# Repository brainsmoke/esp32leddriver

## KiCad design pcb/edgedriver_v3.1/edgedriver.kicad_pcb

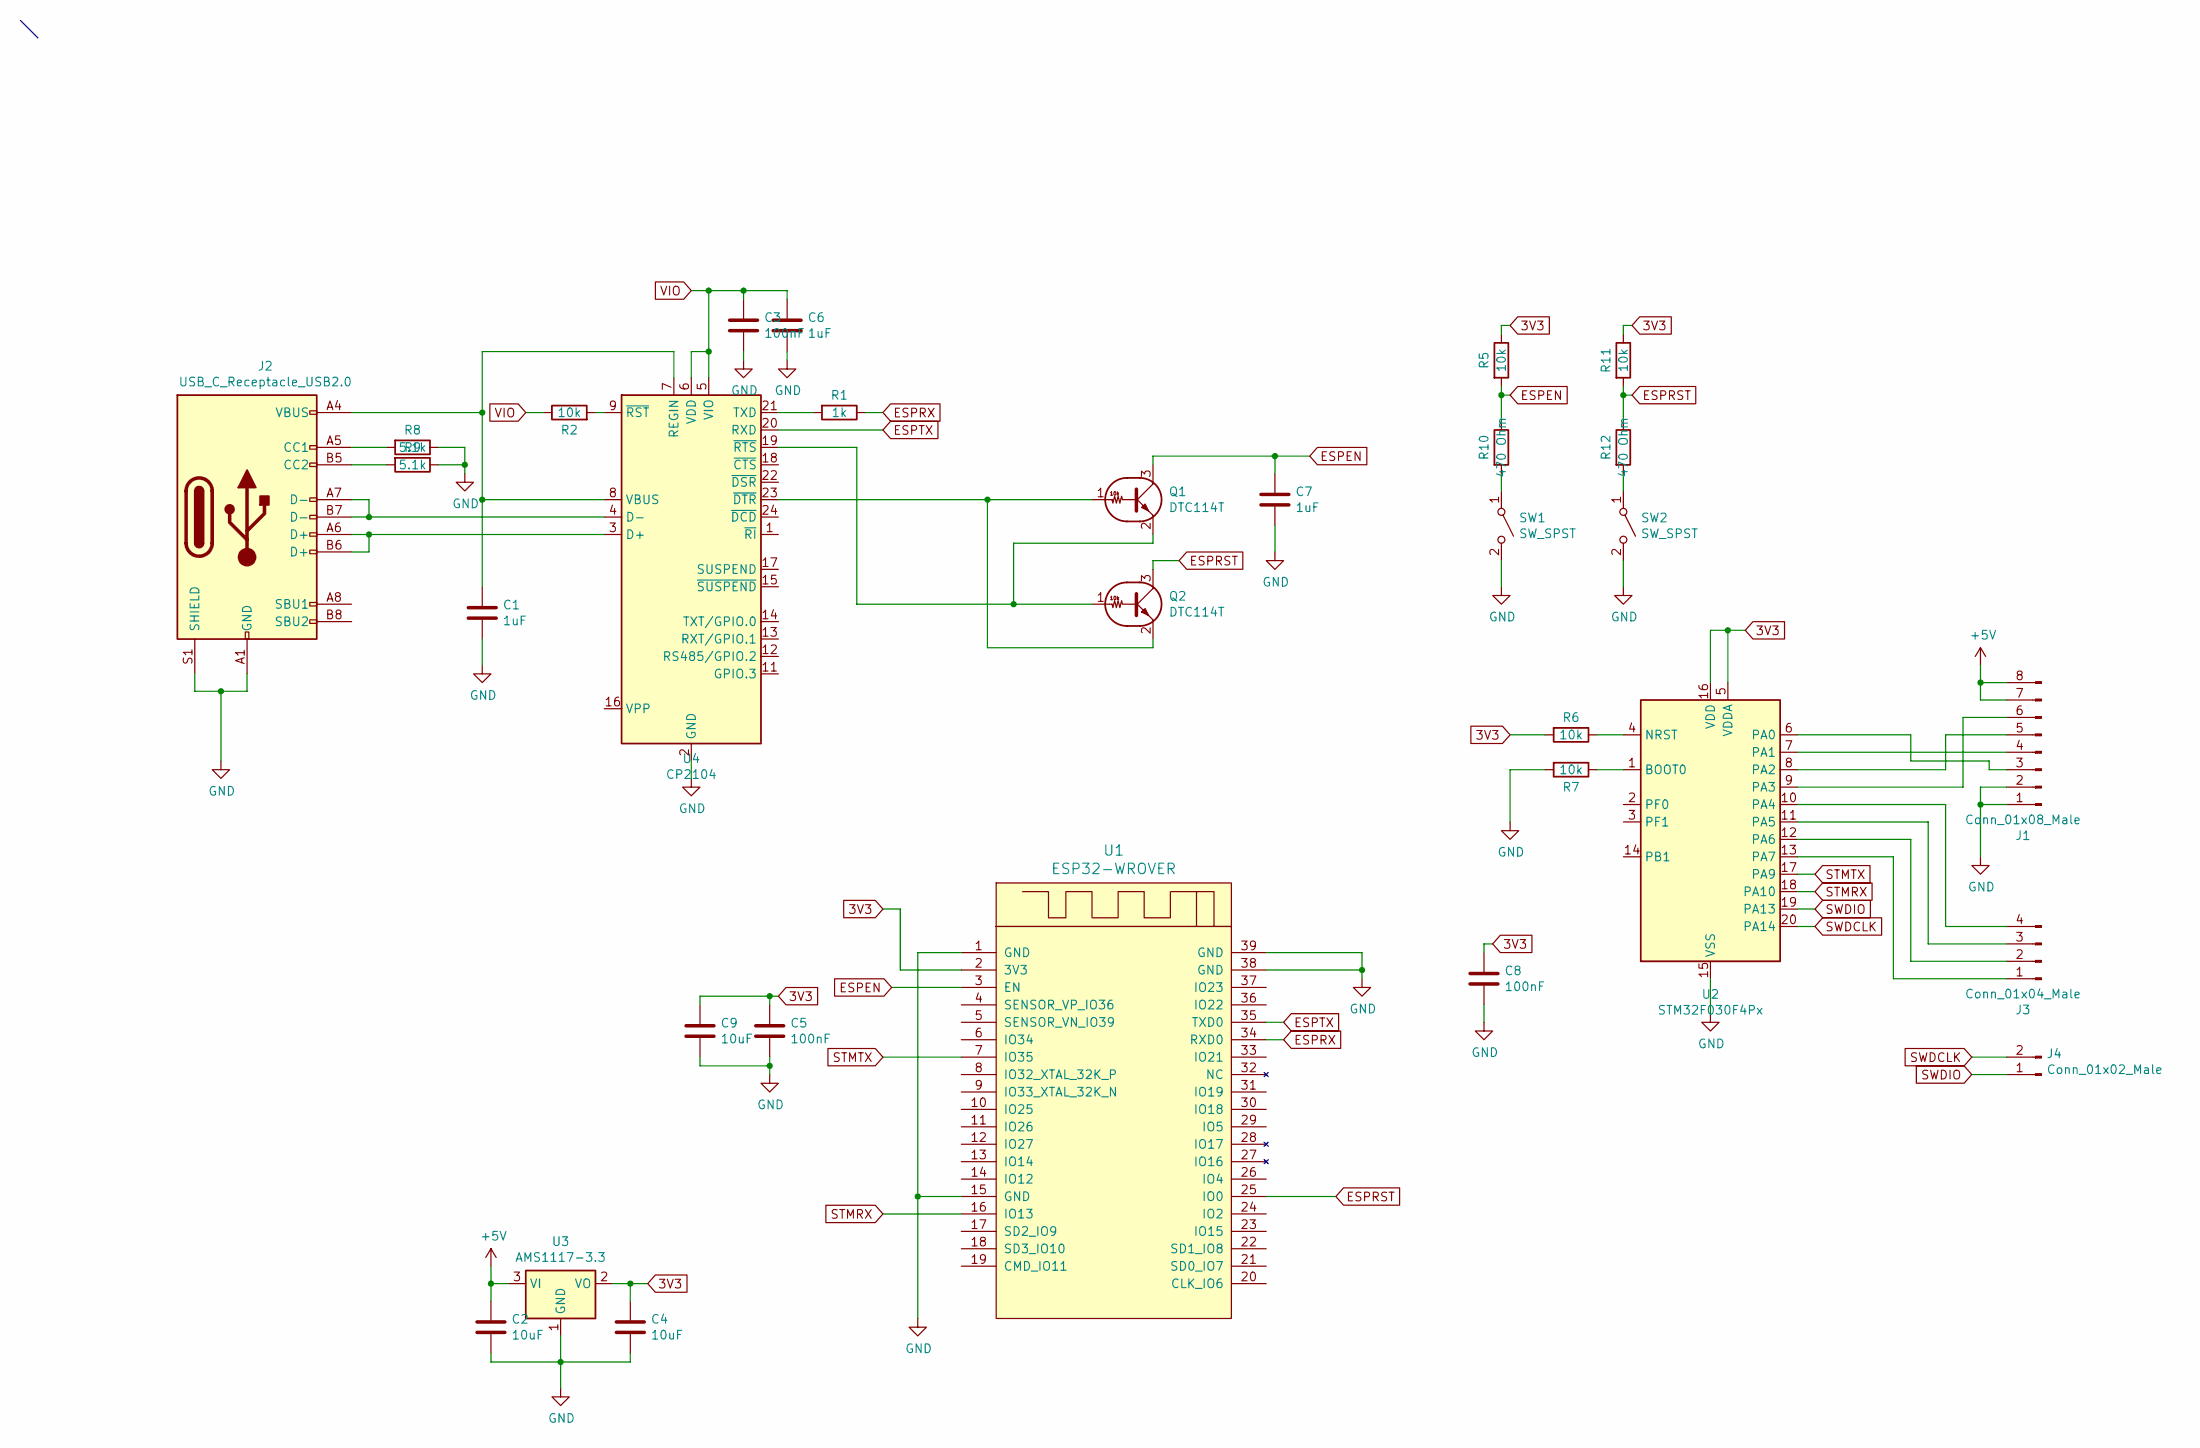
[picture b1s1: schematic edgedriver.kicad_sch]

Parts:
C1, C6, C7: 1uF; C_0402_1005Metric; LCSC C52923
C2, C4, C9: 10uF; C_0805_2012Metric; LCSC C19702
C3, C5, C8: 100nF; C_0402_1005Metric; LCSC C1525
J1: Conn_01x08_Male; PinHeader_1x08_P2.54mm_Vertical
J2: USB_C_Receptacle_USB2.0; USB_C_Receptacle_HRO_TYPE-C-31-M-12
J3: Conn_01x04_Male; PinHeader_1x04_P2.54mm_Vertical
J4: Conn_01x02_Male; PinHeader_1x02_P2.54mm_Vertical
Q1, Q2: DTC114T; SOT-523
R1: 1k; R_0402_1005Metric; LCSC C11702
R2, R5, R6, R7, R11: 10k; R_0402_1005Metric; LCSC C25744
R8, R9: 5.1k; R_0402_1005Metric; LCSC C25905
R10: 470 Ohm; R_0402_1005Metric; LCSC C25792
R12: 470 Ohm; R_0402_1005Metric; LCSC C25167
SW1, SW2: SW_SPST; SW_Push_1P1T_NO_CK_KMR2
U1: ESP32-WROVER; XCVR_ESP32-WROVER
U2: STM32F030F4Px; TSSOP-20_4.4x6.5mm_P0.65mm
U3: AMS1117-3.3; SOT-223-3_TabPin2; LCSC C6186
U4: CP2104; QFN-24-1EP_4x4mm_P0.5mm_EP2.6x2.6mm; LCSC C47742

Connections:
3V3: C4.1, C5.1, C8.1, C9.1, R5.1, R6.2, R11.1, U1.2 (3V3), U2.5 (VDDA), U2.16 (VDD), U3.2 (VO)
+5V: C2.1, J1.7, J1.8, U3.3 (VI)
ESPEN: C7.1, Q1.3 (C), R5.2, R10.1, U1.3 (EN)
ESPRST: Q2.3 (C), R11.2, R12.1, U1.25 (IO0)
ESPRX: R1.1, U1.34 (RXD0)
ESPTX: U1.35 (TXD0), U4.20 (RXD)
GND: C1.2, C2.2, C3.2, C4.2, C5.2, C6.2, C7.2, C8.2, C9.2, J1.1, J1.2, J2.A1 (GND), J2.A12 (GND), J2.B1 (GND), J2.B12 (GND), J2.S1 (SHIELD), R7.2, R8.1, R9.1, SW1.2 (B), SW2.2 (B), U1.1 (GND), U1.15 (GND), U1.38 (GND), U1.39 (GND), U2.15 (VSS), U3.1 (GND), U4.2 (GND), U4.25 (GND)
unnamed: J1.3, U2.6 (PA0)
unnamed: J1.4, U2.7 (PA1)
unnamed: J1.5, U2.8 (PA2)
unnamed: J1.6, U2.9 (PA3)
unnamed: J2.A5 (CC1), R8.2
unnamed: J2.B5 (CC2), R9.2
unnamed: J3.1, U2.13 (PA7)
unnamed: J3.2, U2.12 (PA6)
unnamed: J3.3, U2.11 (PA5)
unnamed: J3.4, U2.10 (PA4)
unnamed: Q1.1 (B), Q2.2 (E), U4.23 (~DTR)
unnamed: Q1.2 (E), Q2.1 (B), U4.19 (~RTS)
unnamed: R10.2, SW1.1 (A)
unnamed: R12.2, SW2.1 (A)
unnamed: R7.1, U2.1 (BOOT0)
unnamed: R6.1, U2.4 (NRST)
unnamed: J2.A6 (D+), J2.B6 (D+), U4.3 (D+)
unnamed: J2.A7 (D-), J2.B7 (D-), U4.4 (D-)
unnamed: C1.1, J2.A4 (VBUS), J2.A9 (VBUS), J2.B4 (VBUS), J2.B9 (VBUS), U4.7 (REGIN), U4.8 (VBUS)
unnamed: R1.2, U4.21 (TXD)
unnamed: R2.2, U4.9 (~RST)
STMRX: U1.16 (IO13), U2.18 (PA10)
STMTX: U1.7 (IO35), U2.17 (PA9)
SWDCLK: J4.2, U2.20 (PA14)
SWDIO: J4.1, U2.19 (PA13)
VIO: C3.1, C6.1, R2.1, U4.5 (VIO), U4.6 (VDD)

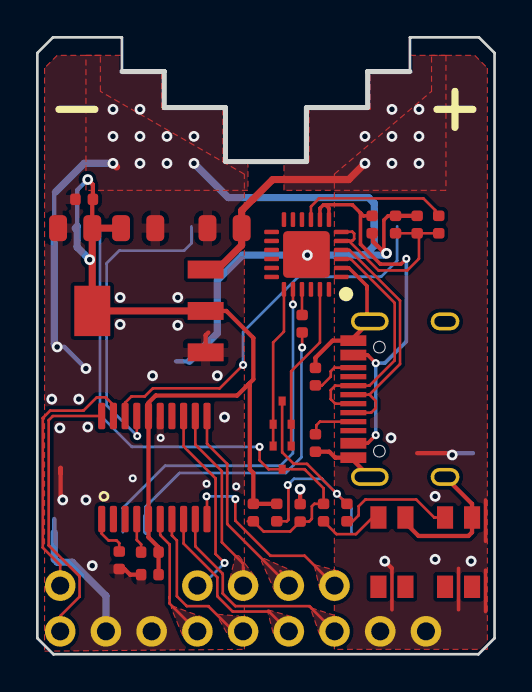
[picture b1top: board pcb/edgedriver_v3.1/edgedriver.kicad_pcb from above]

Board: 4 copper layers, 25.4 x 34.3 mm, 31 parts (1 on the bottom side), 33 nets.

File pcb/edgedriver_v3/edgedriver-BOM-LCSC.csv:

Comment,Designator,Footprint,LCSC Part Number
"10uF","C4,C2,C9","0603","C19702"
"1uF","C7,C6,C1","0603","C15849"
"100nF","C8,C5,C3","0603","C14663"
"AO3400","Q1,Q2","SOT-23-3L","C20917"
"1k","R1","0603","C21190"
"10k","R6,R7,R3,R4,R5,R2","0603","C25804"
"STM32F030F4P6","U2","TSSOP-20_4.4x6.5x0.65P","C89040"
"AMS1117-3.3","U3","SOT-223","C6186"
"CP2104","U4","QFN-24_EP_4.0x4.0x0.5P","C47742"

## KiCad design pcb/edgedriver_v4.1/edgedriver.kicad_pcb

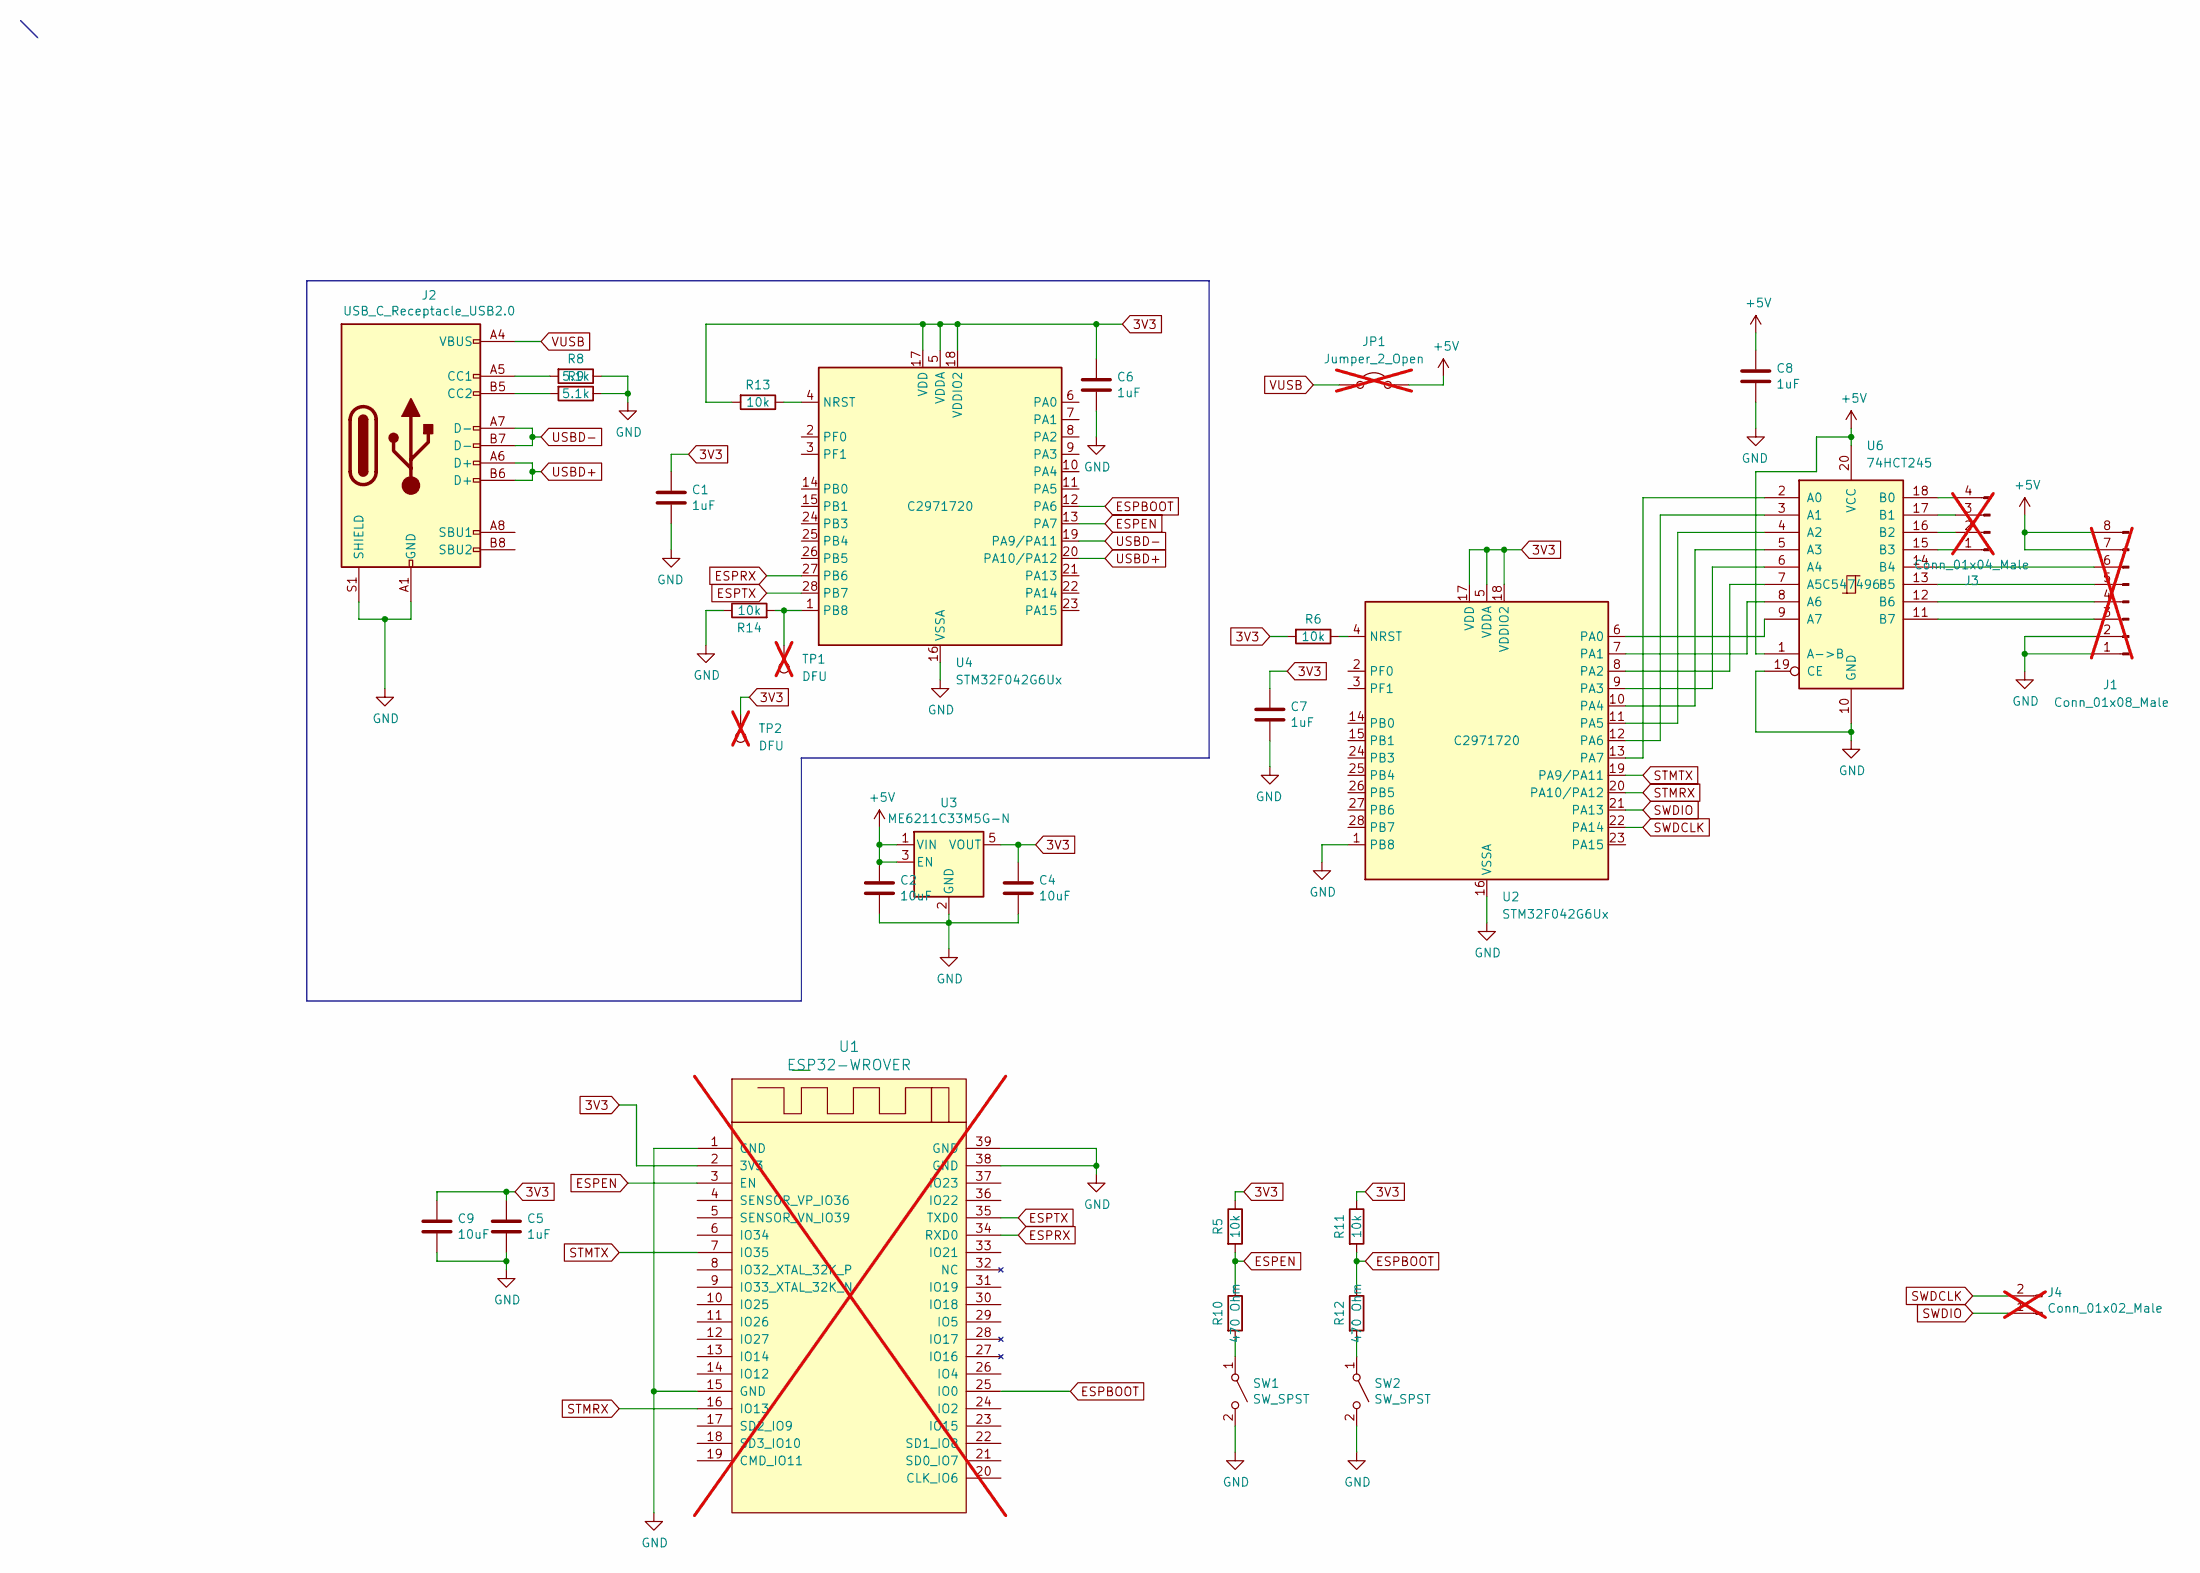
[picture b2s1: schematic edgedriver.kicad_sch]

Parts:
C1, C5, C6, C7, C8: 1uF; C_0402_1005Metric; LCSC C52923
C2, C4, C9: 10uF; C_0603_1608Metric; LCSC C19702
J1: Conn_01x08_Male; PinHeader_1x08_P2.54mm_Vertical; not fitted
J2: USB_C_Receptacle_USB2.0; USB_C_Receptacle_HRO_TYPE-C-31-M-12; LCSC C165948
J3: Conn_01x04_Male; PinHeader_1x04_P2.54mm_Vertical; not fitted
J4: Conn_01x02_Male; PinHeader_1x02_P2.54mm_Vertical; not fitted
JP1: Jumper_2_Open; R_0805_2012Metric; not fitted
R5, R6, R11, R13, R14: 10k; R_0402_1005Metric; LCSC C25744
R8, R9: 5.1k; R_0402_1005Metric; LCSC C25905
R10, R12: 470 Ohm; R_0402_1005Metric; LCSC C25117
SW1, SW2: SW_SPST; SW_Push_1P1T_NO_CK_KMR2; LCSC C318893
TP1, TP2: DFU; TestPoint_Pad_D1.0mm; not fitted
U1: ESP32-WROVER; XCVR_ESP32-WROVER; not fitted
U2, U4: STM32F042G6Ux; QFN-28_4x4mm_P0.5mm; LCSC C2971720
U3: ME6211C33M5G-N; SOT-23-5; LCSC C82942
U6: 74HCT245; DHVQFN-20-1EP_2.5x4.5mm_P0.5mm_EP1x3mm; LCSC C547496

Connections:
3V3: C1.1, C4.1, C5.1, C6.1, C7.1, C9.1, R5.1, R6.2, R11.1, R13.2, TP2.1, U1.2 (3V3), U2.5 (VDDA), U2.17 (VDD), U2.18 (VDDIO2), U3.5 (VOUT), U4.5 (VDDA), U4.17 (VDD), U4.18 (VDDIO2)
+5V: C2.1, C8.1, J1.7, J1.8, JP1.2 (B), U3.1 (VIN), U3.3 (EN), U6.1 (A->B), U6.20 (VCC)
ESPBOOT: R11.2, R12.1, U1.25 (IO0), U4.12 (PA6)
ESPEN: R5.2, R10.1, U1.3 (EN), U4.13 (PA7)
ESPRX: U1.34 (RXD0), U4.27 (PB6)
ESPTX: U1.35 (TXD0), U4.28 (PB7)
GND: C1.2, C2.2, C4.2, C5.2, C6.2, C7.2, C8.2, C9.2, J1.1, J1.2, J2.A1 (GND), J2.A12 (GND), J2.B1 (GND), J2.B12 (GND), J2.S1 (SHIELD), R8.1, R9.1, R14.1, SW1.2 (B), SW2.2 (B), U1.1 (GND), U1.15 (GND), U1.38 (GND), U1.39 (GND), U2.1 (PB8), U2.16 (VSSA), U3.2 (GND), U4.16 (VSSA), U6.10 (GND), U6.19 (CE)
unnamed: J1.3, U6.11 (B7)
unnamed: J1.4, U6.12 (B6)
unnamed: J1.5, U6.13 (B5)
unnamed: J1.6, U6.14 (B4)
unnamed: J2.A5 (CC1), R8.2
unnamed: J2.B5 (CC2), R9.2
unnamed: J3.1, U6.15 (B3)
unnamed: J3.2, U6.16 (B2)
unnamed: J3.3, U6.17 (B1)
unnamed: J3.4, U6.18 (B0)
unnamed: R10.2, SW1.1 (A)
unnamed: R12.2, SW2.1 (A)
unnamed: R6.1, U2.4 (NRST)
unnamed: U2.6 (PA0), U6.9 (A7)
unnamed: U2.7 (PA1), U6.8 (A6)
unnamed: U2.8 (PA2), U6.7 (A5)
unnamed: U2.9 (PA3), U6.6 (A4)
unnamed: U2.10 (PA4), U6.5 (A3)
unnamed: U2.11 (PA5), U6.4 (A2)
unnamed: U2.12 (PA6), U6.3 (A1)
unnamed: U2.13 (PA7), U6.2 (A0)
unnamed: R13.1, U4.4 (NRST)
unnamed: R14.2, TP1.1, U4.1 (PB8)
STMRX: U1.16 (IO13), U2.20 (PA10/PA12)
STMTX: U1.7 (IO35), U2.19 (PA9/PA11)
SWDCLK: J4.2, U2.22 (PA14)
SWDIO: J4.1, U2.21 (PA13)
USBD+: J2.A6 (D+), J2.B6 (D+), U4.20 (PA10/PA12)
USBD-: J2.A7 (D-), J2.B7 (D-), U4.19 (PA9/PA11)
VUSB: J2.A4 (VBUS), J2.A9 (VBUS), J2.B4 (VBUS), J2.B9 (VBUS), JP1.1 (A)

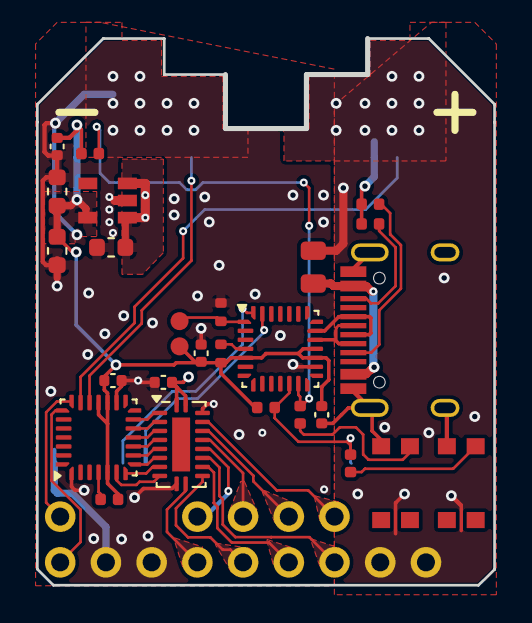
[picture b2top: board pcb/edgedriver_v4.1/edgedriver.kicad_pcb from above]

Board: 4 copper layers, 25.4 x 30.4 mm, 31 parts (1 on the bottom side), 37 nets.

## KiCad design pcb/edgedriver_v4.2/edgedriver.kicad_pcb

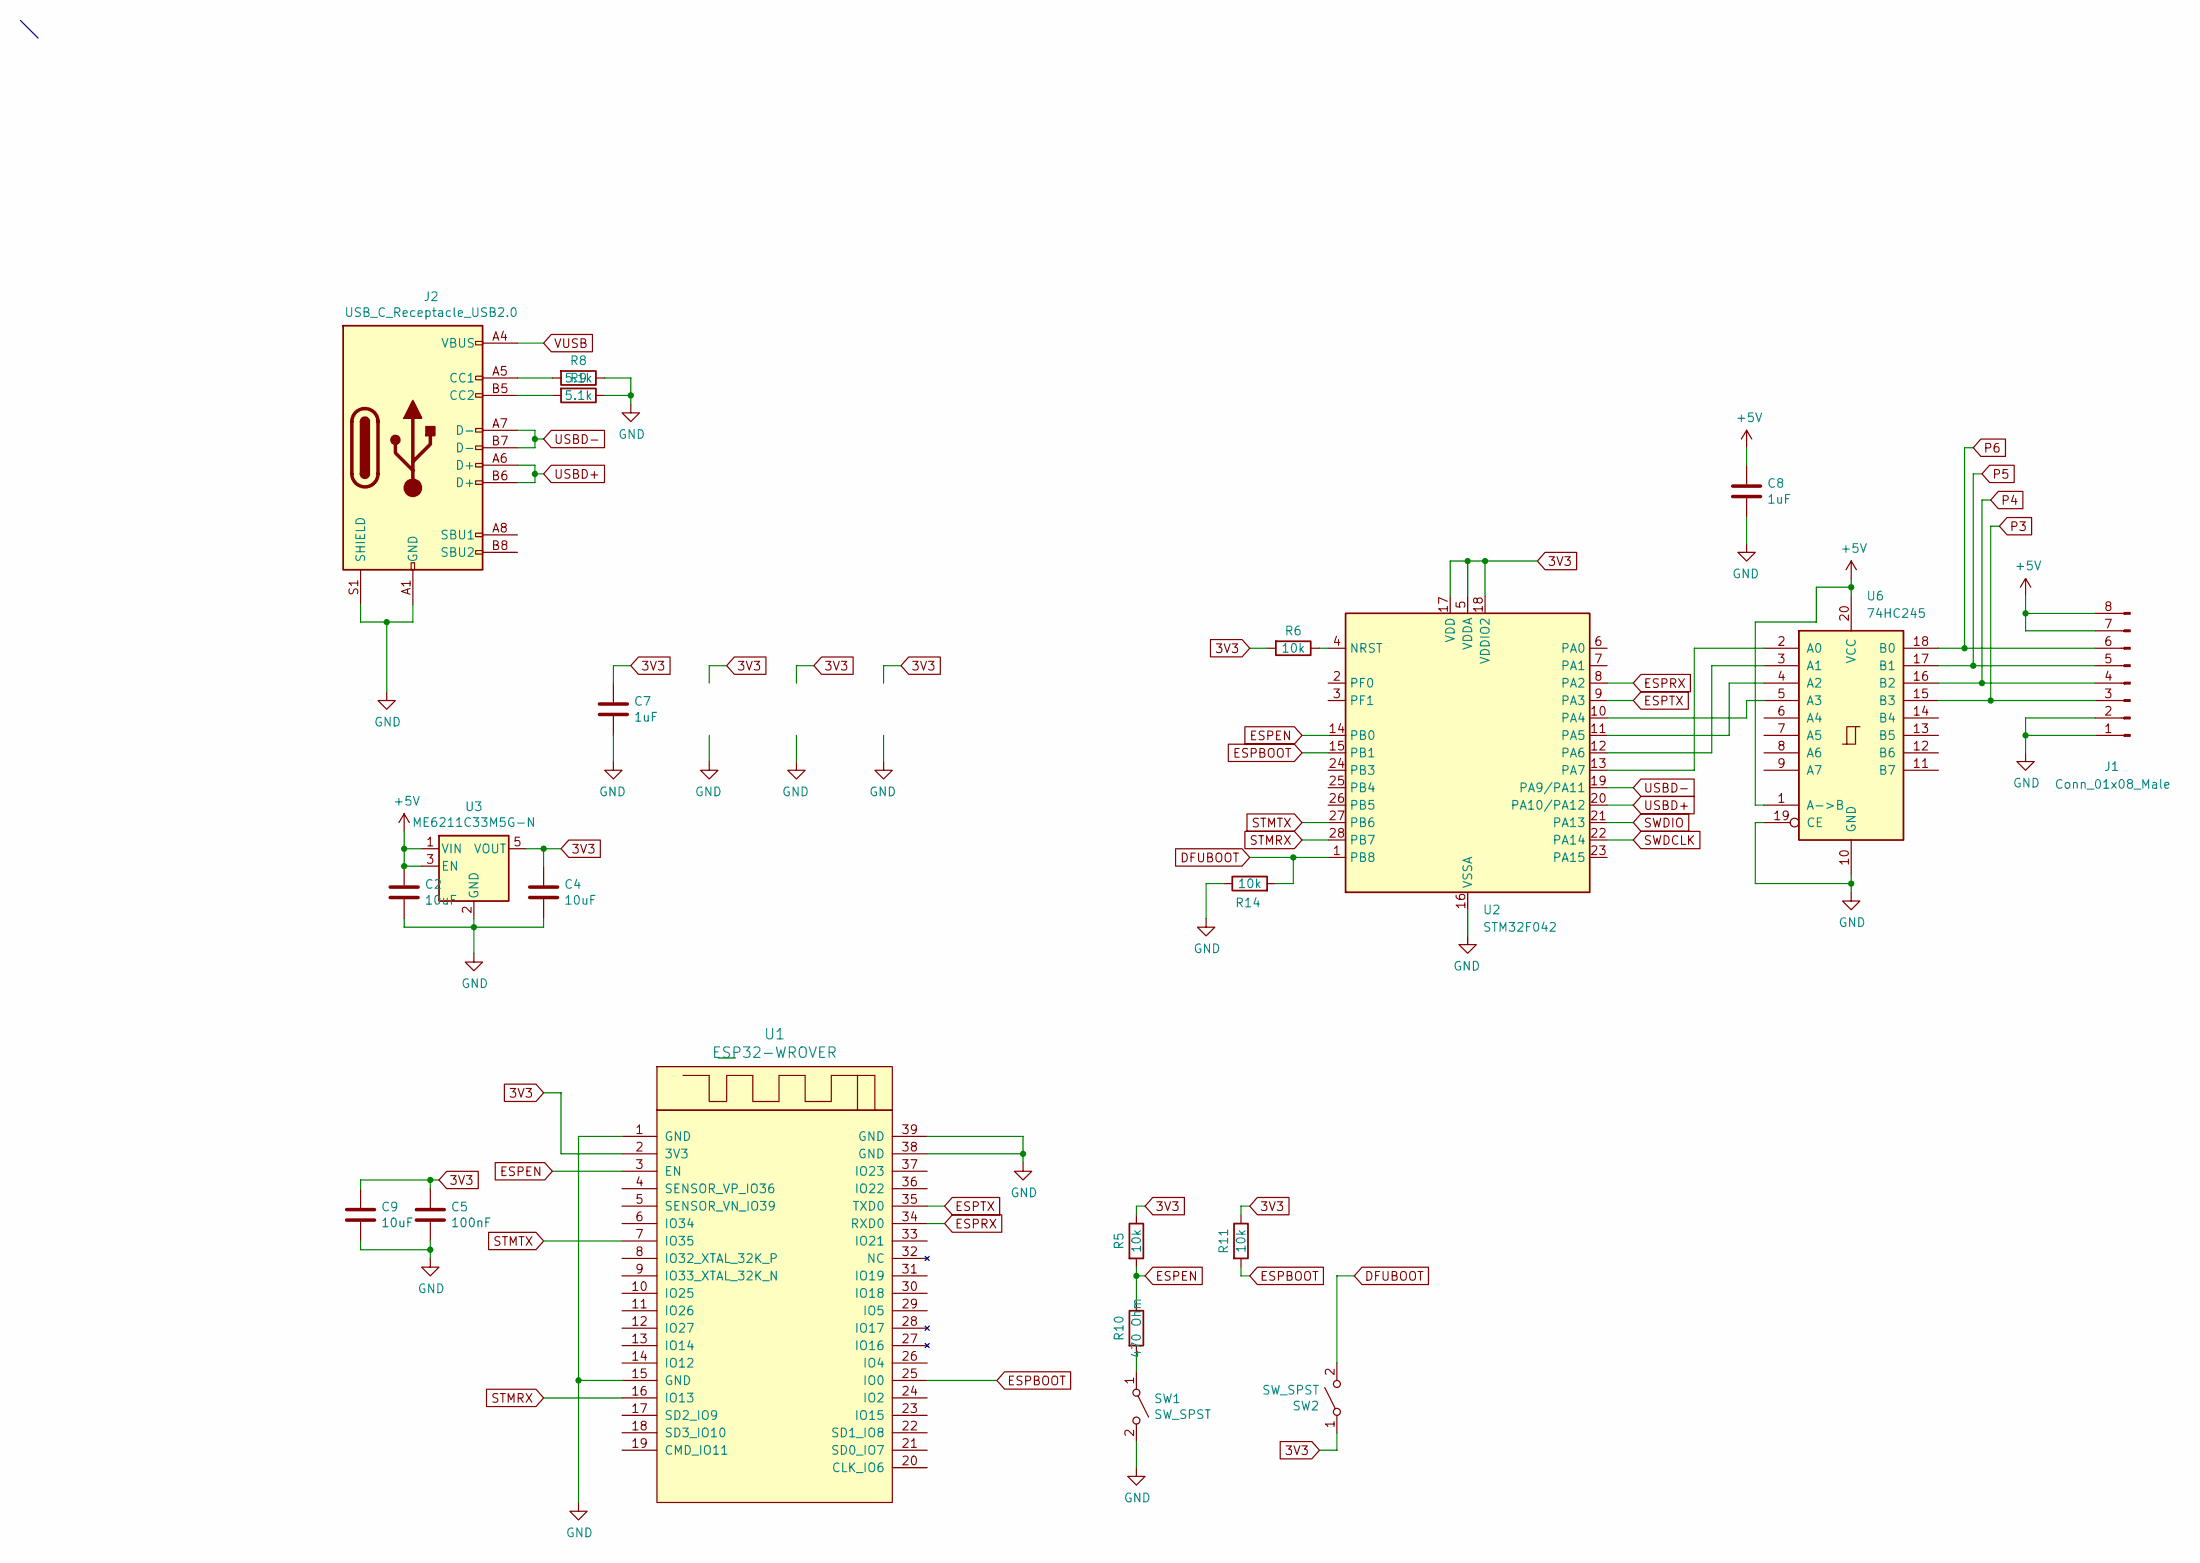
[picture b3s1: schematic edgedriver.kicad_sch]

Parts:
C2, C4, C9: 10uF; C_0603_1608Metric; LCSC C19702
C5: 100nF; C_0402_1005Metric; LCSC C1525
C7, C8: 1uF; C_0402_1005Metric; LCSC C52923
J1: Conn_01x08_Male; PinHeader_1x08_P2.54mm_Vertical
J2: USB_C_Receptacle_USB2.0; USB_C_Receptacle_HRO_TYPE-C-31-M-12; LCSC C165948
R5, R6, R11, R14: 10k; R_0402_1005Metric; LCSC C25744
R8, R9: 5.1k; R_0402_1005Metric; LCSC C25905
R10: 470 Ohm; R_0402_1005Metric; LCSC C25117
SW1, SW2: SW_SPST; SW_Push_1P1T_NO_CK_KMR2; LCSC C318893
U1: ESP32-WROVER; XCVR_ESP32-WROVER
U2: STM32F042; QFN-28_4x4mm_P0.5mm
U3: ME6211C33M5G-N; SOT-23-5; LCSC C82942
U6: 74HC245; DHVQFN-20-1EP_2.5x4.5mm_P0.5mm_EP1x3mm

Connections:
3V3: C4.1, C5.1, C7.1, C9.1, R5.1, R6.2, R11.1, SW2.1 (A), U1.2 (3V3), U2.5 (VDDA), U2.17 (VDD), U2.18 (VDDIO2), U3.5 (VOUT)
+5V: C2.1, C8.1, J1.7, J1.8, U3.1 (VIN), U3.3 (EN), U6.1 (A->B), U6.20 (VCC)
DFUBOOT: R14.2, SW2.2 (B), U2.1 (PB8)
ESPBOOT: R11.2, U1.25 (IO0), U2.15 (PB1)
ESPEN: R5.2, R10.1, U1.3 (EN), U2.14 (PB0)
ESPRX: U1.34 (RXD0), U2.8 (PA2)
ESPTX: U1.35 (TXD0), U2.9 (PA3)
GND: C2.2, C4.2, C5.2, C7.2, C8.2, C9.2, J1.1, J1.2, J2.A1 (GND), J2.A12 (GND), J2.B1 (GND), J2.B12 (GND), J2.S1 (SHIELD), R8.1, R9.1, R14.1, SW1.2 (B), U1.1 (GND), U1.15 (GND), U1.38 (GND), U1.39 (GND), U2.16 (VSSA), U3.2 (GND), U6.10 (GND), U6.19 (CE)
unnamed: J2.A5 (CC1), R8.2
unnamed: J2.B5 (CC2), R9.2
unnamed: R10.2, SW1.1 (A)
unnamed: R6.1, U2.4 (NRST)
unnamed: U2.10 (PA4), U6.5 (A3)
unnamed: U2.11 (PA5), U6.4 (A2)
unnamed: U2.12 (PA6), U6.3 (A1)
unnamed: U2.13 (PA7), U6.2 (A0)
P3: J1.3, U6.15 (B3)
P4: J1.4, U6.16 (B2)
P5: J1.5, U6.17 (B1)
P6: J1.6, U6.18 (B0)
STMRX: U1.16 (IO13), U2.28 (PB7)
STMTX: U1.7 (IO35), U2.27 (PB6)
SWDCLK: U2.22 (PA14)
SWDIO: U2.21 (PA13)
USBD+: J2.A6 (D+), J2.B6 (D+), U2.20 (PA10/PA12)
USBD-: J2.A7 (D-), J2.B7 (D-), U2.19 (PA9/PA11)
VUSB: J2.A4 (VBUS), J2.A9 (VBUS), J2.B4 (VBUS), J2.B9 (VBUS)

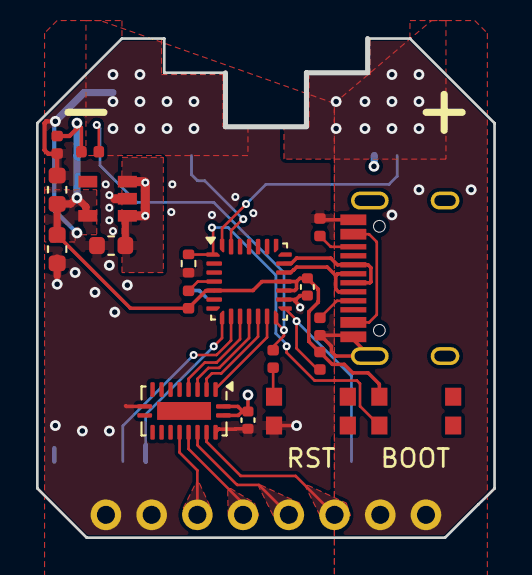
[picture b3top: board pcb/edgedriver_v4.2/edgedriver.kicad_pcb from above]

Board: 4 copper layers, 25.4 x 27.7 mm, 21 parts (1 on the bottom side), 25 nets.

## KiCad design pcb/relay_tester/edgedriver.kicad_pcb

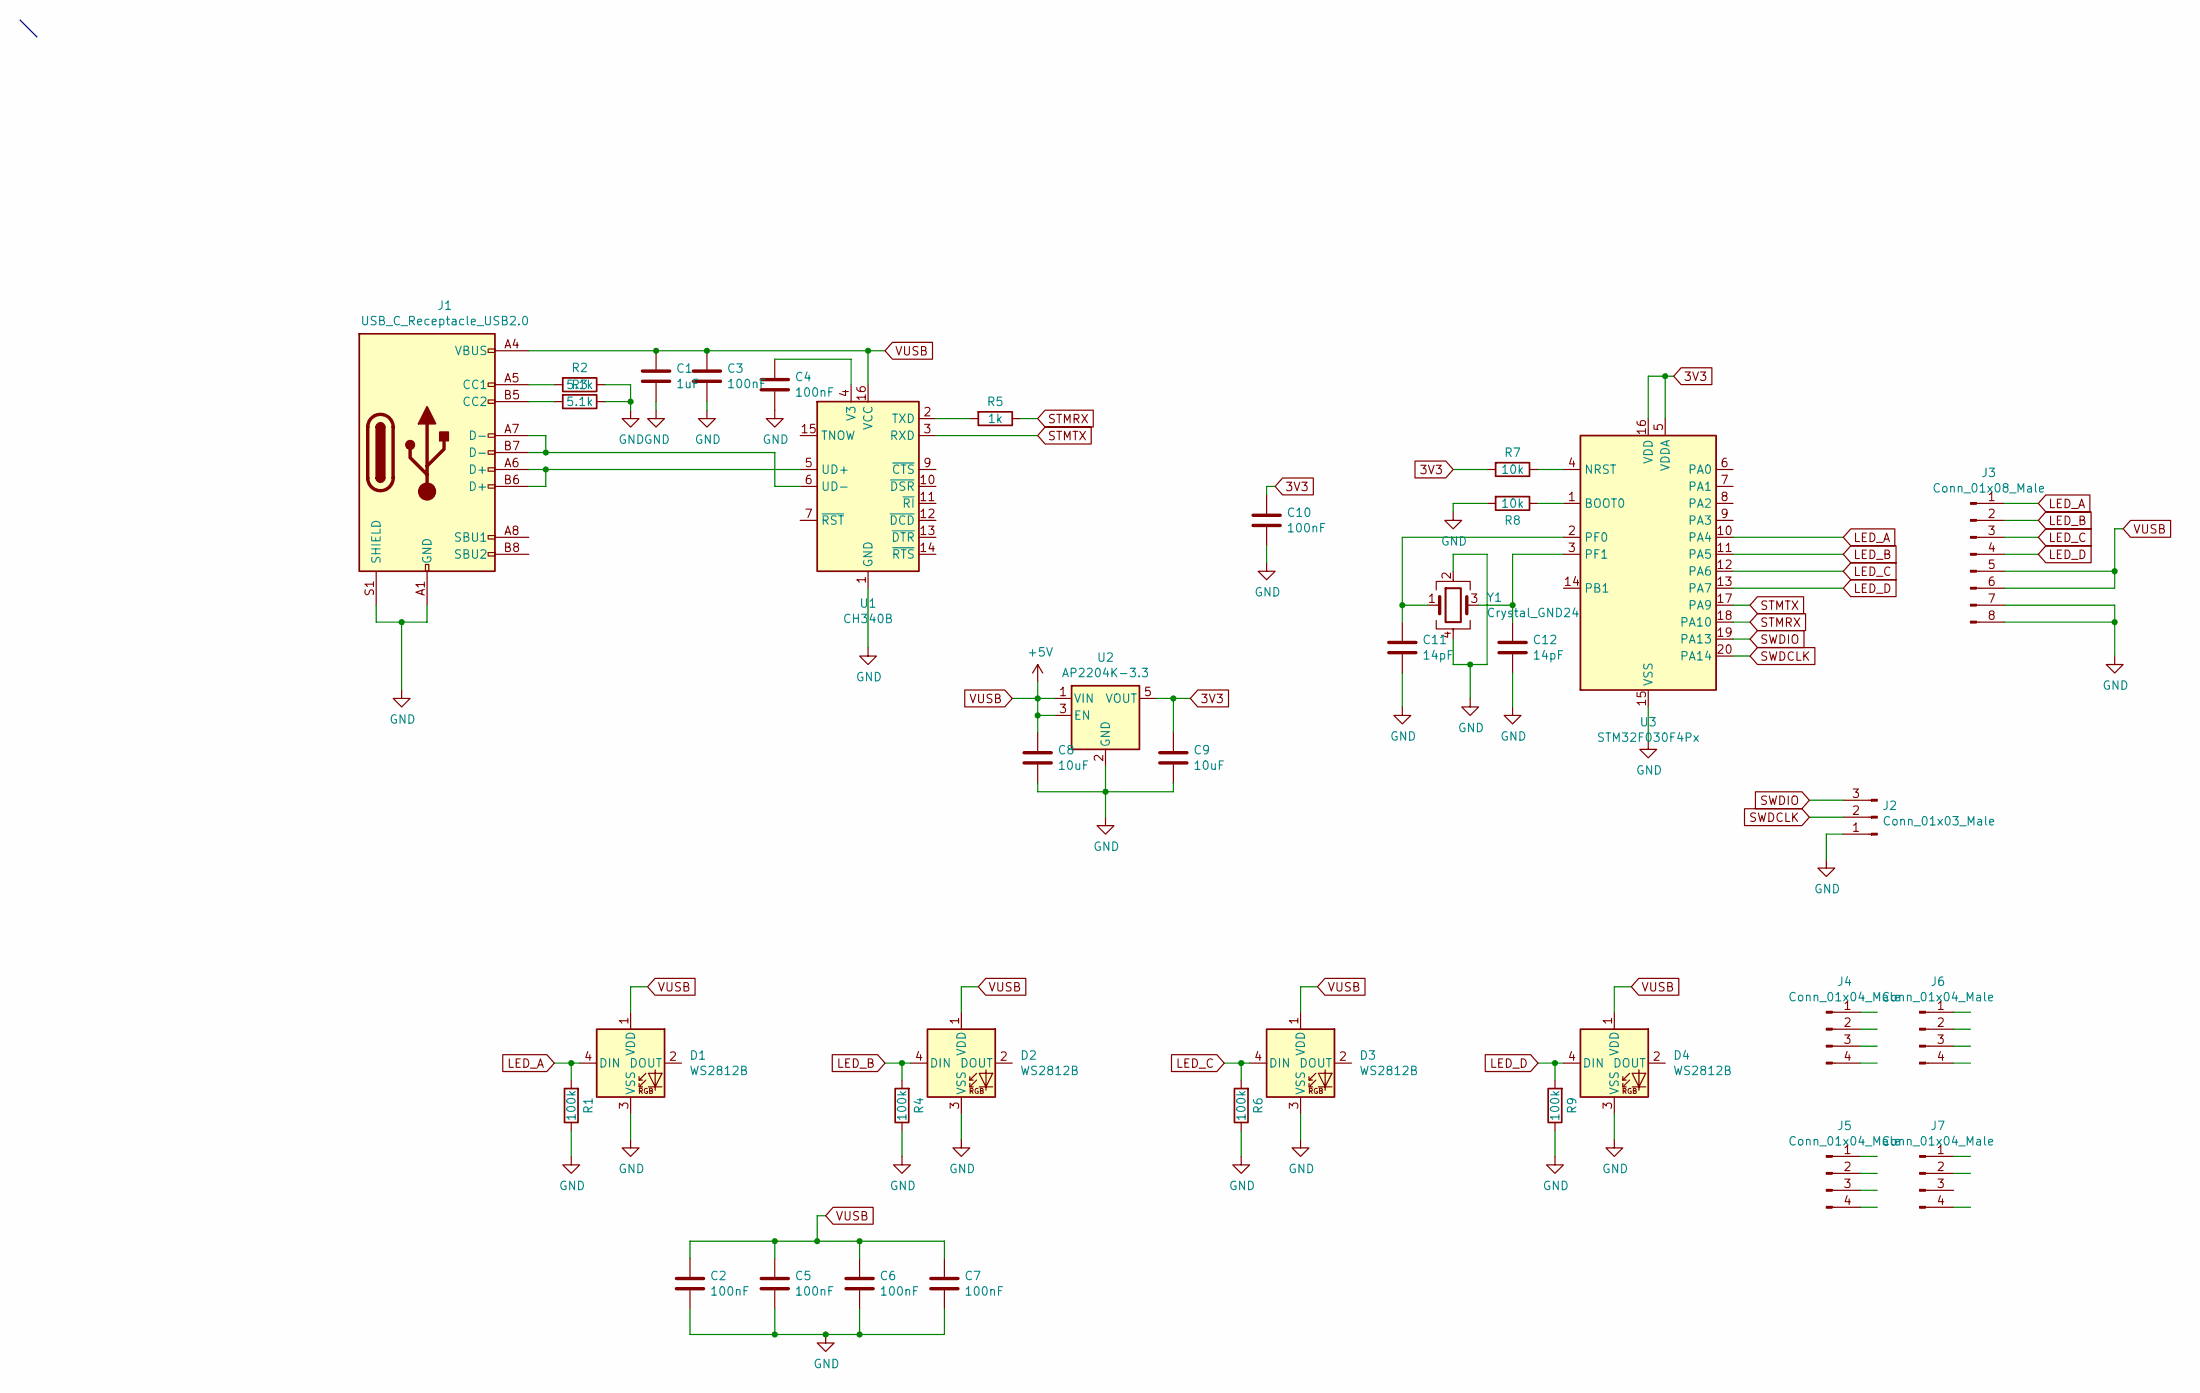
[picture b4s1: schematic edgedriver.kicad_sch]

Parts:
C1: 1uF; C_0603_1608Metric_Pad1.08x0.95mm_HandSolder; LCSC C52923
C2, C3, C4, C5, C6, C7, C10: 100nF; C_0603_1608Metric_Pad1.08x0.95mm_HandSolder; LCSC C1525
C8, C9: 10uF; C_0603_1608Metric_Pad1.08x0.95mm_HandSolder; LCSC C19702
C11, C12: 14pF; C_0603_1608Metric_Pad1.08x0.95mm_HandSolder; LCSC C19702
D1, D2, D3, D4: WS2812B; LED_WS2812B_PLCC4_5.0x5.0mm_P3.2mm
J1: USB_C_Receptacle_USB2.0; USB_C_Receptacle_HRO_TYPE-C-31-M-12
J2: Conn_01x03_Male; PinHeader_1x03_P2.54mm_Vertical
J3: Conn_01x08_Male; padauk_test_a
J4, J5, J6, J7: Conn_01x04_Male; PinHeader_1x04_P2.54mm_Vertical
R1, R4, R6, R9: 100k; R_0603_1608Metric_Pad0.98x0.95mm_HandSolder; LCSC C11702
R2, R3: 5.1k; R_0603_1608Metric_Pad0.98x0.95mm_HandSolder; LCSC C25905
R5: 1k; R_0603_1608Metric_Pad0.98x0.95mm_HandSolder; LCSC C11702
R7, R8: 10k; R_0603_1608Metric_Pad0.98x0.95mm_HandSolder; LCSC C25744
U1: CH340B; SOIC-16_3.9x9.9mm_P1.27mm
U2: AP2204K-3.3; SOT-23-5
U3: STM32F030F4Px; TSSOP-20_4.4x6.5mm_P0.65mm
Y1: Crystal_GND24; TSX-3225

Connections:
3V3: C9.1, C10.1, R7.2, U2.5 (VOUT), U3.5 (VDDA), U3.16 (VDD)
GND: C1.2, C2.2, C3.2, C4.2, C5.2, C6.2, C7.2, C8.2, C9.2, C10.2, C11.2, C12.2, D1.3 (VSS), D2.3 (VSS), D3.3 (VSS), D4.3 (VSS), J1.A1 (GND), J1.A12 (GND), J1.B1 (GND), J1.B12 (GND), J1.S1 (SHIELD), J2.1, J3.7, J3.8, R1.1, R2.1, R3.1, R4.1, R6.1, R8.2, R9.1, U1.1 (GND), U2.2 (GND), U3.15 (VSS), Y1.2, Y1.4
LED_A: D1.4 (DIN), J3.1, R1.2, U3.10 (PA4)
LED_B: D2.4 (DIN), J3.2, R4.2, U3.11 (PA5)
LED_C: D3.4 (DIN), J3.3, R6.2, U3.12 (PA6)
LED_D: D4.4 (DIN), J3.4, R9.2, U3.13 (PA7)
unnamed: J1.A5 (CC1), R2.2
unnamed: J1.B5 (CC2), R3.2
unnamed: R5.2, U1.2 (TXD)
unnamed: J1.A6 (D+), J1.B6 (D+), U1.5 (UD+)
unnamed: J1.A7 (D-), J1.B7 (D-), U1.6 (UD-)
unnamed: C4.1, U1.4 (V3)
unnamed: R8.1, U3.1 (BOOT0)
unnamed: R7.1, U3.4 (NRST)
unnamed: C11.1, U3.2 (PF0), Y1.1
unnamed: C12.1, U3.3 (PF1), Y1.3
STMRX: R5.1, U3.18 (PA10)
STMTX: U1.3 (RXD), U3.17 (PA9)
SWDCLK: J2.2, U3.20 (PA14)
SWDIO: J2.3, U3.19 (PA13)
VUSB: C1.1, C2.1, C3.1, C5.1, C6.1, C7.1, C8.1, D1.1 (VDD), D2.1 (VDD), D3.1 (VDD), D4.1 (VDD), J1.A4 (VBUS), J1.A9 (VBUS), J1.B4 (VBUS), J1.B9 (VBUS), J3.5, J3.6, U1.16 (VCC), U2.1 (VIN), U2.3 (EN)

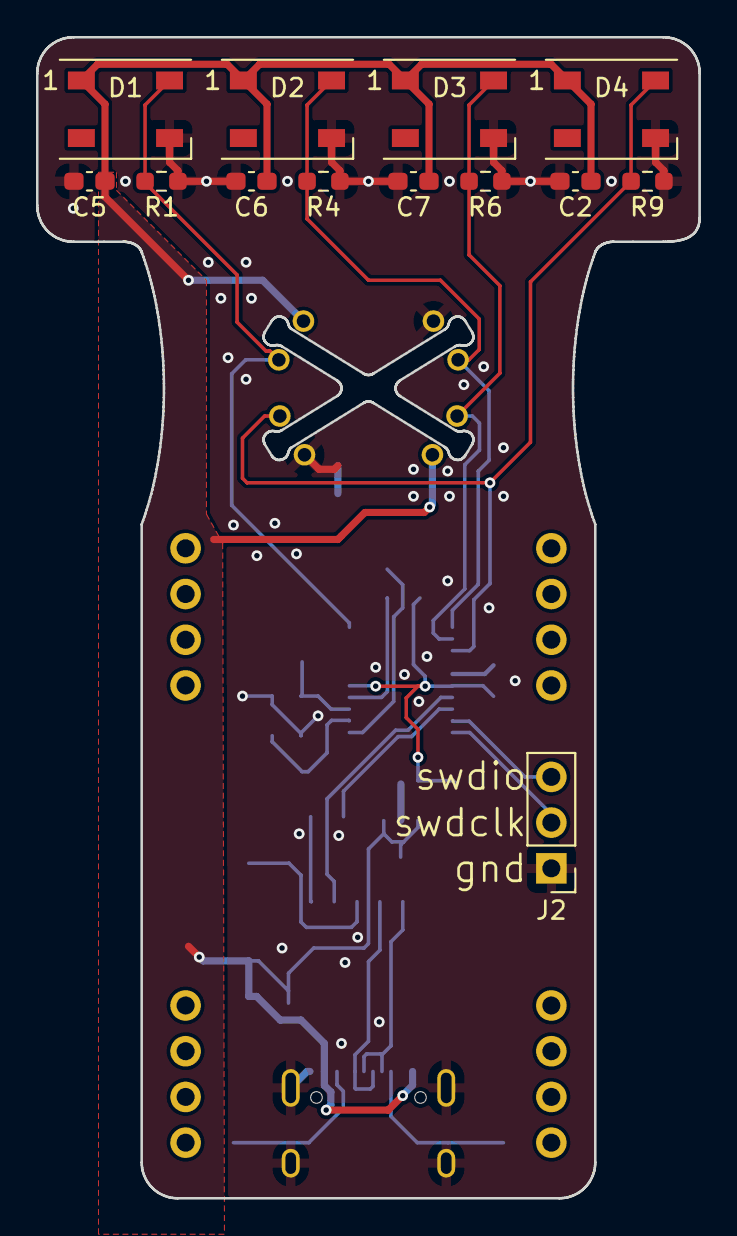
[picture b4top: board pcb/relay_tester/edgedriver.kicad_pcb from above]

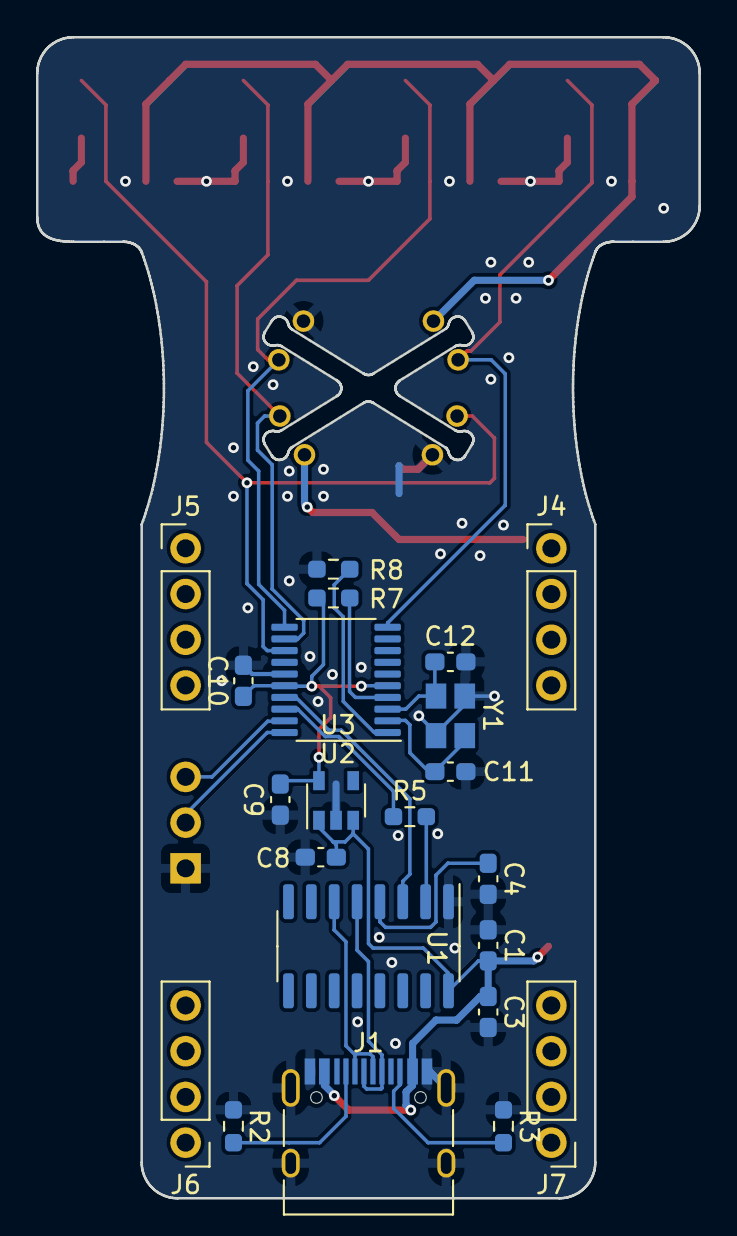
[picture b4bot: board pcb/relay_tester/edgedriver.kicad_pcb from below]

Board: 2 copper layers, 36.8 x 64.5 mm, 36 parts (22 on the bottom side), 21 nets.
